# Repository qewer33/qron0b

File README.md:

**qron0b** is a minimalist and low-power digital **binary wristwatch**. It uses an **Attiny24A/44A/84A as it's MCU**, uses the **DS1302 as it's RTC** and displays the time in **BCD (binary coded decimal)** format with it's integrated **4x4 LED matrix driven by an 74HC595 shift register**. It's powered by a single **CR2032 coin cell battery**. It's designed to use minimal power and **can run without a battery change for months**.

> [!WARNING]  
> This project is NOT perfect by any means, it's my first ever low-power board design and thus contains many design flaws (although mostly small). It does work but build it at your own risk and definitely don't expect everything to go smoothly.

## Repository Layout
- [pcb/](https://github.com/qewer33/qron0b/tree/main/pcb): The KiCAD project for the qron0b PCB.
- [cad/](https://github.com/qewer33/qron0b/tree/main/cad): The FreeCAD files (and .stl + .step for 3D printing) for the watch case.
- [firmware/](https://github.com/qewer33/qron0b/tree/main/firmware): The source code for the qron0b firmware, written in bare metal AVR C.
- [assets/](https://github.com/qewer33/qron0b/tree/main/assets) Screenshots and render files used in the README.

## The Product

### Features

qron0b's default firmware is very minimalistic and thus only contains two basic features: **reading time** and **setting time**. The watch is in the sleep state by default with the CPU in power-down mode and the display off. When the onboard button is clicked, the CPU is wakes up from sleep and displays the current time in the LED matrix for 10 seconds. The time can be set while the watch is awake by long pressing the onboard button. Both features are explained in detail under the next two headings.

### Reading Time

The time is displayed in BCD (binary coded decimal) format on qron0b's 4x4 LED matrix in columns (HH:MM), with the LSB (least-significant bit) being the bottom-most LED. Meaning for each column; the bottom-most LED represents 1, the one above represents 2, two above represents 4 and the top-most LED represents 8. All LEDs being off in a column represents 0. The first column is the tens digit of hour, the second column is the ones digit of hour, third column is the tens digit of minute and the fourth column is the ones digit of minute.

Below is a visual explanation and a few examples to help explain it better:

### Setting Time

The time can be set while the watch is awake by long pressing the onboard button. The whole LED matrix will flash for ~0.5 seconds to indicate entering edit mode. After the watch enters edit mode, the first column (tens digit of hour) will start flashing (it may not flash if it's 0). Press the button once to increment the current column/digits value (it will wrap automatically, eg. between 0-2 for tens digit of hour or 0-5 for the tens digit of minute). After setting the current digit to the desired value, long press the button to move on to the next digit (the next column will start flashing). Long pressing on the last digit/column (the ones column of minute) will save the newly set time to the RTC and exit edit mode.

## Hardware

### PCB Design

The qron0b PCB is designed in the free and open source EDA software, KiCAD. You can find the PCB design source files under [pcb/](https://github.com/qewer33/qron0b/tree/main/pcb).

### Mechanical Design

The mechanical parts of qron0b (the watch casing) is designed in the free and open source CAD software, FreeCAD. The watch case is designed in 2 parts: the bottom base and the top "glass". They connect together via a simple clip system. The bottom base casing accepts 22mm GT2/GT3 style watch straps.

You can find the CAD source and 3D print files under [cad/](https://github.com/qewer33/qron0b/tree/main/cad).

## Firmware

The qron0b firmware is written in bare-metal AVR C. It's written to be as minimal as possible and is only 1916 bytes, meaning it can even run on the ATtiny24A (in fact, it's designed for the 24A!).

For more information on the firmware, see the README.md file inside [firmware/](https://github.com/qewer33/qron0b/tree/main/firmware).

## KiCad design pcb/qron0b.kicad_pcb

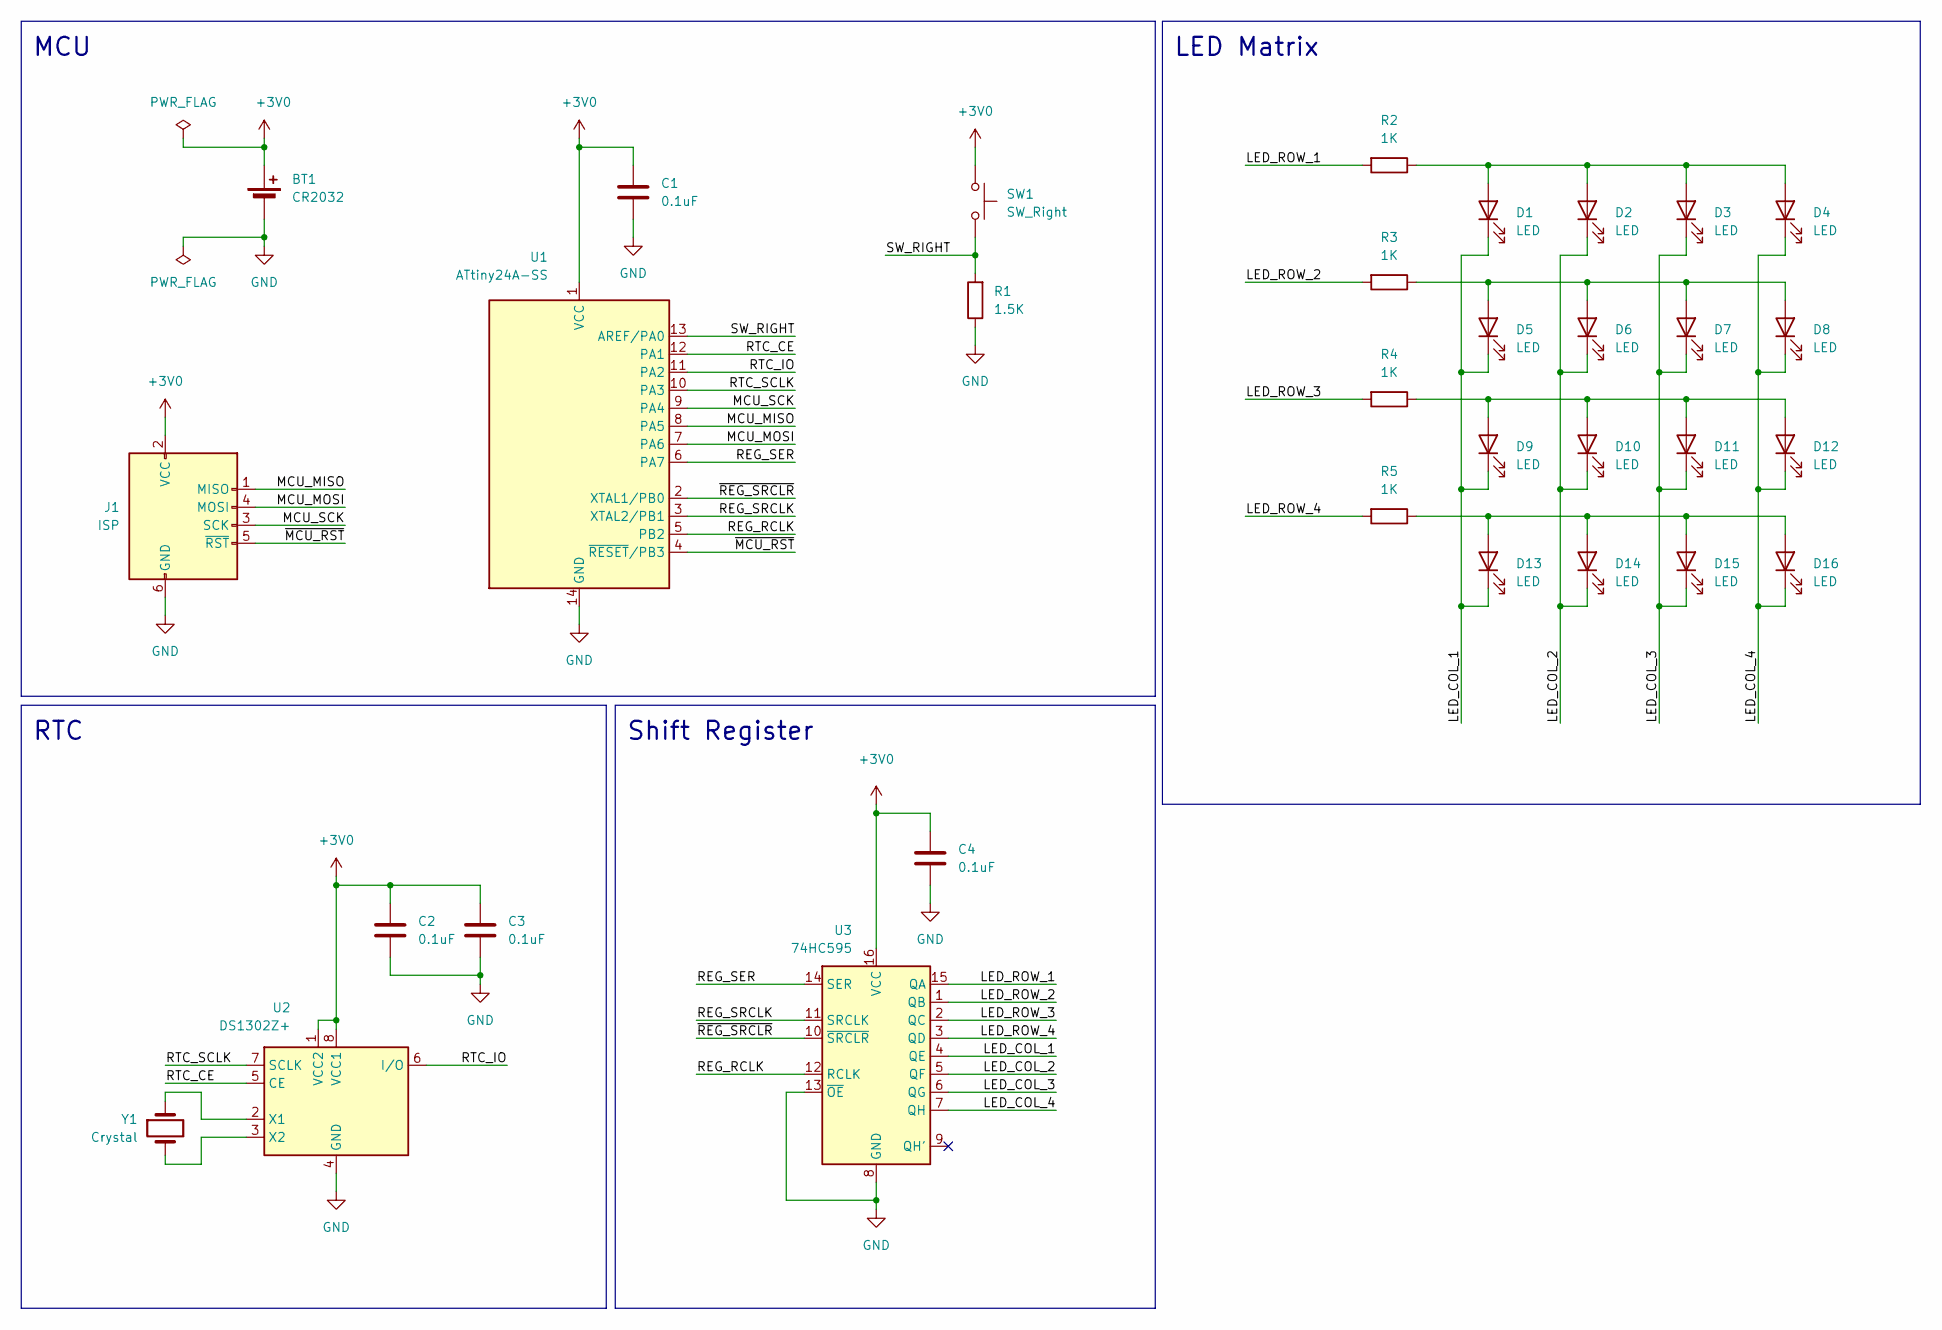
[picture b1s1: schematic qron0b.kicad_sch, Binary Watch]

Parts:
BT1: CR2032; BatteryHolder_Multicomp_BC-2001_1x2032
C1, C2, C3, C4: 0.1uF; C_1206_3216Metric_Pad1.33x1.80mm_HandSolder
D1, D2, D3, D4, D5, D6, D7, D8, D9, D10, D11, D12, D13, D14, D15, D16: LED; LED_1206_3216Metric_Pad1.42x1.75mm_HandSolder
J1: ISP; PinHeader_2x03_P2.54mm_Vertical
R1: 1.5K; R_1206_3216Metric_Pad1.30x1.75mm_HandSolder
R2, R3, R4, R5: 1K; R_1206_3216Metric_Pad1.30x1.75mm_HandSolder
SW1: SW_Right; SW_Tactile_SPST_NO_Straight_CK_PTS636Sx25SMTRLFS
U1: ATtiny24A-SS; SOIC-14_3.9x8.7mm_P1.27mm
U2: DS1302Z+; SOIC-8_3.9x4.9mm_P1.27mm
U3: 74HC595; SOIC-16_3.9x9.9mm_P1.27mm
Y1: Crystal; Crystal_C38-LF_D3.0mm_L8.0mm_Horizontal

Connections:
+3V0: BT1.1 (+), C1.1, C2.1, C3.1, C4.1, J1.2 (VCC), SW1.2, U1.1 (VCC), U2.1 (VCC2), U2.8 (VCC1), U3.16 (VCC); also elsewhere on the board
/LED_COL_1: D1.1 (K), D5.1 (K), D9.1 (K), D13.1 (K), U3.4 (QE)
/LED_COL_2: D2.1 (K), D6.1 (K), D10.1 (K), D14.1 (K), U3.5 (QF)
/LED_COL_3: D3.1 (K), D7.1 (K), D11.1 (K), D15.1 (K), U3.6 (QG)
/LED_COL_4: D4.1 (K), D8.1 (K), D12.1 (K), D16.1 (K), U3.7 (QH)
/LED_ROW_1: R2.2, U3.15 (QA)
/LED_ROW_2: R3.2, U3.1 (QB)
/LED_ROW_3: R4.2, U3.2 (QC)
/LED_ROW_4: R5.2, U3.3 (QD)
/MCU_MISO: J1.1 (MISO), U1.8 (PA5); also elsewhere on the board
/MCU_MOSI: J1.4 (MOSI), U1.7 (PA6); also elsewhere on the board
/MCU_SCK: J1.3 (SCK), U1.9 (PA4); also elsewhere on the board
/REG_RCLK: U1.5 (PB2), U3.12 (RCLK)
/REG_SER: U1.6 (PA7), U3.14 (SER)
/REG_SRCLK: U1.3 (XTAL2/PB1), U3.11 (SRCLK)
/RTC_CE: U1.12 (PA1), U2.5 (CE)
/RTC_IO: U1.11 (PA2), U2.6 (I/O)
/RTC_SCLK: U1.10 (PA3), U2.7 (SCLK)
/SW_RIGHT: R1.2, SW1.1, U1.13 (AREF/PA0); also elsewhere on the board
/~MCU_RST: J1.5 (~RST), U1.4 (~RESET/PB3); also elsewhere on the board
/~REG_SRCLR: U1.2 (XTAL1/PB0), U3.10 (~SRCLR)
GND: BT1.2 (-), C1.2, C2.2, C3.2, C4.2, J1.6 (GND), R1.1, U1.14 (GND), U2.4 (GND), U3.8 (GND), U3.13 (~OE); also elsewhere on the board
unnamed: D1.2 (A), D2.2 (A), D3.2 (A), D4.2 (A), R2.1
unnamed: D5.2 (A), D6.2 (A), D7.2 (A), D8.2 (A), R3.1
unnamed: D9.2 (A), D10.2 (A), D11.2 (A), D12.2 (A), R4.1
unnamed: D13.2 (A), D14.2 (A), D15.2 (A), D16.2 (A), R5.1
unnamed: U2.2 (X1), Y1.1
unnamed: U2.3 (X2), Y1.2

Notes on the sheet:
Shift Register
MCU
LED Matrix
RTC

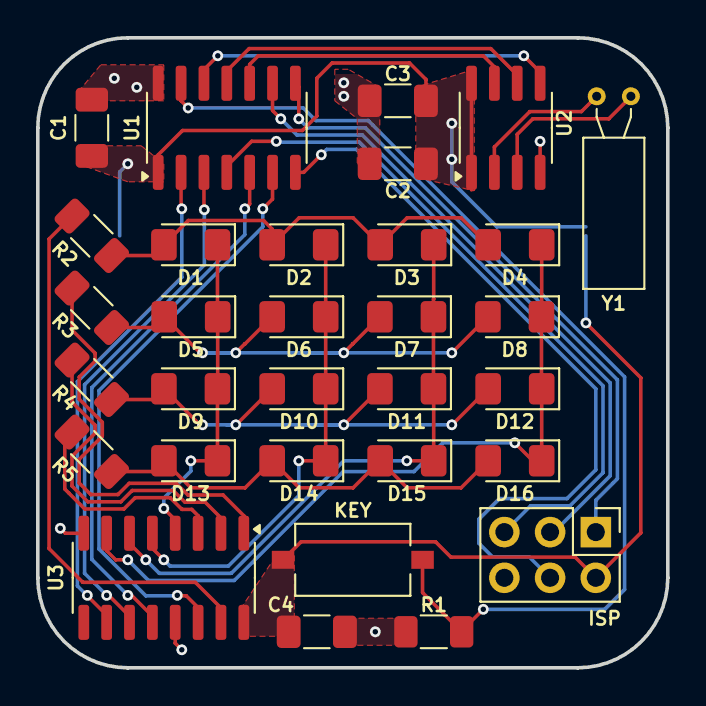
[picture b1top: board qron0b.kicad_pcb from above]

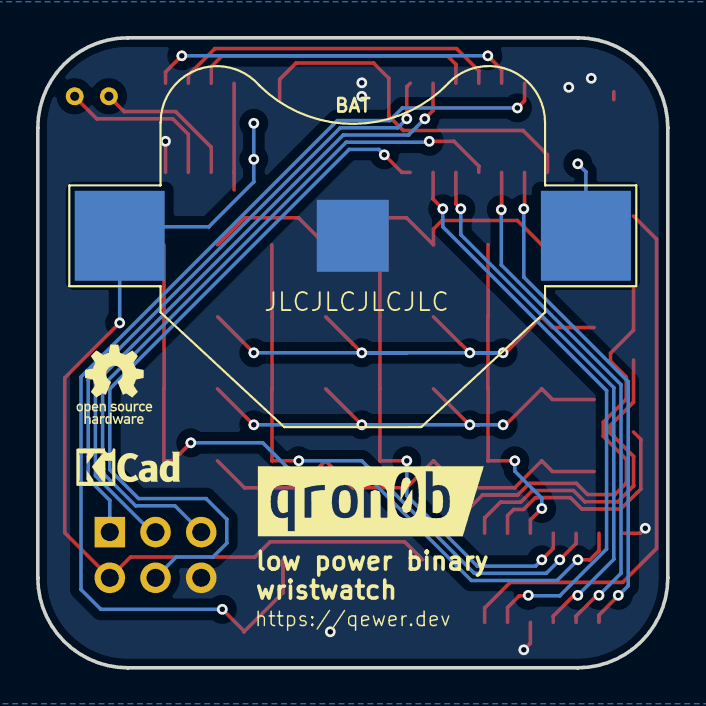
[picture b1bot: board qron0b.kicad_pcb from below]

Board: 2 copper layers, 35.0 x 35.0 mm, 33 parts (2 on the bottom side), 28 nets.

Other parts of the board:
BAT: CR2032; BatteryHolder_Multicomp_BC-2001_1x2032
ISP: ISP; PinHeader_2x03_P2.54mm_Vertical
KEY: SW_Right; SW_Tactile_SPST_NO_Straight_CK_PTS636Sx25SMTRLFS
kibuzzard-678832A4: G***; kibuzzard-678832A4

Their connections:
+3V0: BAT.1 (+), ISP.2 (VCC), KEY.2; also elsewhere on the board
/MCU_MISO: ISP.1 (MISO); also elsewhere on the board
/MCU_MOSI: ISP.4 (MOSI); also elsewhere on the board
/MCU_SCK: ISP.3 (SCK); also elsewhere on the board
/SW_RIGHT: KEY.1; also elsewhere on the board
/~MCU_RST: ISP.5 (~RST); also elsewhere on the board
GND: BAT.2 (-), ISP.6 (GND); also elsewhere on the board

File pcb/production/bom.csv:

Designator,Footprint,Quantity,Value,LCSC Part #
BAT,BatteryHolder_Multicomp_BC-2001_1x2032,1,CR2032,
"C1, C2, C3, C4",1206,4,0.1uF,
"D1, D10, D11, D12, D13, D14, D15, D16, D2, D3, D4, D5, D6, D7, D8, D9",1206,16,LED,
ISP,PinHeader_2x03_P2.54mm_Vertical,1,ISP,
KEY,SW_Tactile_SPST_NO_Straight_CK_PTS636Sx25SMTRLFS,1,SW_Right,
R1,1206,1,1.5K,
"R2, R3, R4, R5",1206,4,1K,
U1,SOIC-14_3.9x8.7mm_P1.27mm,1,ATtiny24A-SS,
U2,SOIC-8_3.9x4.9mm_P1.27mm,1,DS1302Z+,
U3,SOIC-16_3.9x9.9mm_P1.27mm,1,74HC595,
Y1,Crystal_C38-LF_D3.0mm_L8.0mm_Horizontal,1,Crystal,

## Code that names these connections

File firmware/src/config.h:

#pragma once

#define F_CPU 1000000UL // 1 MHz clock

// Pin definitions
#define KEY PA0

// Shift register pins
#define REG_SER PA7
#define REG_SRCLK PB1
#define REG_RCLK PB2
#define REG_SRCLR PB0

// RTC pins
#define RTC_CE PA1
#define RTC_SCLK PA3
#define RTC_IO PA2

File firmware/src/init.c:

#include "gpio.h"
#include "matrix.h"
#include "rtc.h"

#include <avr/interrupt.h>
#include <avr/sleep.h>
#include <util/delay.h>

// Disable unused peripherals
void disable_unused() {
    ADCSRA &= ~(1 << ADEN); // Disable ADC
    PRR |= (1 << PRADC) | (1 << PRUSI) | (1 << PRTIM0); // Power down unused blocks
    ACSR |= (1 << ACD); // Disable analog comparator
    // Ouput & LOW proramming pins
    PIN_OUTPUT(DDRA, PA4);
    PIN_OUTPUT(DDRA, PA5);
    PIN_OUTPUT(DDRA, PA6);
    PIN_LOW(PORTA, PA4);
    PIN_LOW(PORTA, PA5);
    PIN_LOW(PORTA, PA6);

    // Disable digital input buffers on unused ADC pins
    DIDR0 |= (1 << ADC1D) | (1 << ADC3D) | (1 << ADC4D)
          | (1 << ADC5D) | (1 << ADC6D) | (1 << ADC7D);
}

// Configure PB0 as the wake-up pin
void setup_wakeup_pin() {
    // Set KEY as input
    PIN_INPUT(DDRA, KEY);
    PIN_LOW(PORTA, KEY);

    // Enable interrupts
    PCMSK0 |= (1 << PCINT0);
    GIMSK |= (1 << PCIE0);
}

// Initialize timer (TIM1)
void timer_init() {
    // Reset control registers
    TCCR1A = 0;
    TCCR1B = 0;

    // Set compare match value
    // 1000 ticks at 1MHz = ISR triggers every 1ms
    OCR1A = 999;

    TCCR1B |= (1 << WGM12); // CTC mode
    TCCR1B |= (1 << CS10); // No prescaling
    TIMSK1 |= (1 << OCIE1A); // Enable COMPA interrupt
}

// Set CPU to deep sleep
void enter_deep_sleep() {
    // Setup shift register for sleep
    shift_register_write(0xF0);
    PIN_LOW(PORTB, REG_SRCLK);
    PIN_LOW(PORTB, REG_RCLK);
    PIN_LOW(PORTA, REG_SER);
    PIN_HIGH(PORTB, REG_SRCLR); // Keep reset deasserted

    // Park pins to reduce leakage during sleep
    PIN_LOW(PORTA, RTC_CE);
    PIN_LOW(PORTA, RTC_SCLK);
    PIN_INPUT(DDRA, RTC_IO);
    PIN_LOW(PORTA, RTC_IO);

    // Set sleep mode settings
    set_sleep_mode(SLEEP_MODE_PWR_DOWN);
    sleep_enable();
    GIFR |= (1 << PCIF0); // Clear any pending pin-change interrupt

    // Sleep...
    sleep_cpu();

    // After sleep
    sleep_disable();
    rtc_init(); // Restore RTC pins
    shift_register_init(); // Restore shift register
}

// Util to parse __TIME__ macro (__TIME__ is "HH:MM:SS")
static uint8_t parse_two_digit(const char *s) {
    return (uint8_t) ((s[0] - '0') * 10 + (s[1] - '0'));
}

// Read compile time from __TIME__ macro
void get_compile_time(uint8_t* h, uint8_t* m, uint8_t* s) {
    *h = parse_two_digit(&__TIME__[0]);
    *m = parse_two_digit(&__TIME__[3]);
    *s = parse_two_digit(&__TIME__[6]);
}

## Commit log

2025-12-17 Add .gitattributes
2025-12-20 Firmware updates
2025-12-23 Add .gitignore
2025-12-23 Add Makefile
2025-12-24 Update README and Makefile
2025-12-24 Update Makefile
2025-12-26 Update photo
2025-12-27 Firmware: Tweak init.c for power saving
2025-12-27 Assets: Add board photo
2026-01-04 Fix typo in README.md for BCD explanation
    bir-> bit
2026-01-04 Firmware: Minimize delays
2026-01-06 Improve README
